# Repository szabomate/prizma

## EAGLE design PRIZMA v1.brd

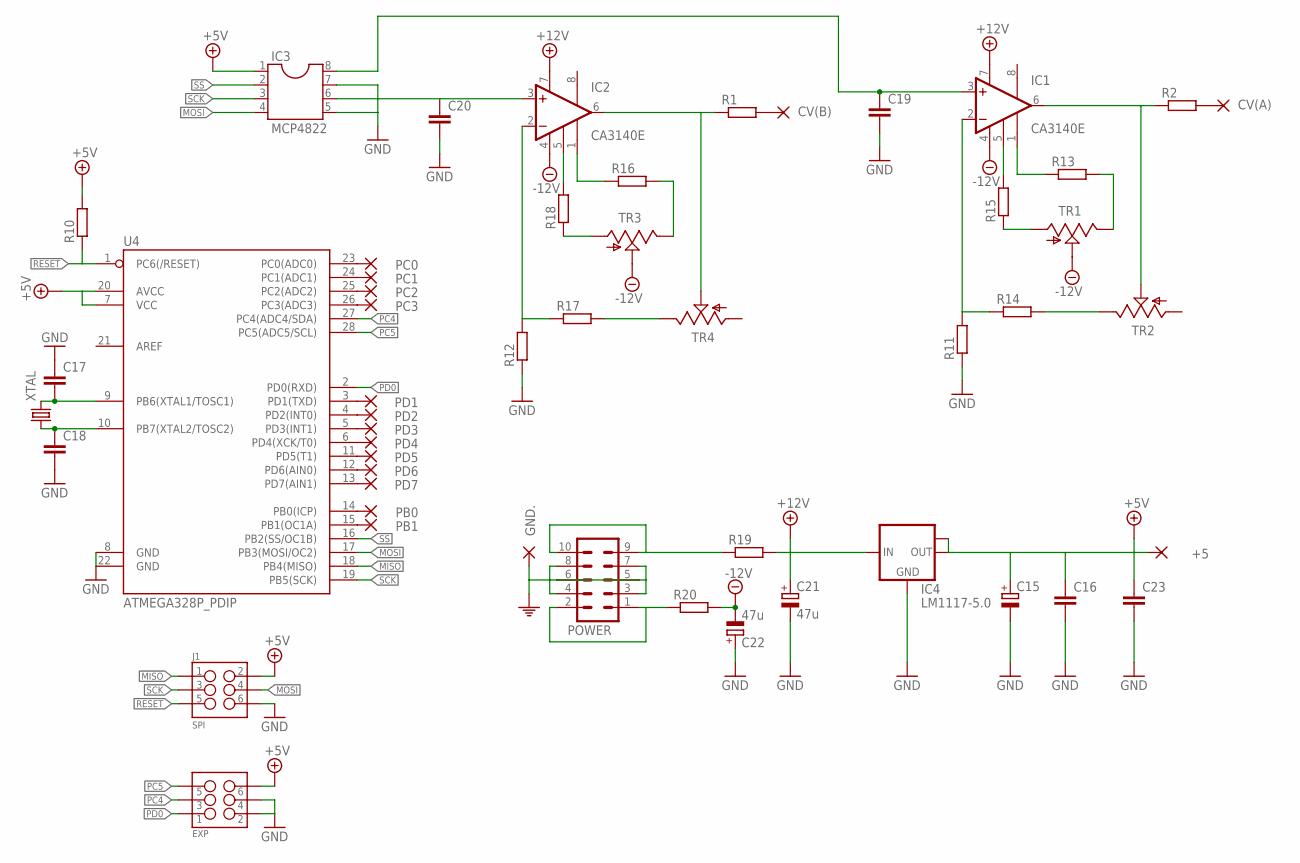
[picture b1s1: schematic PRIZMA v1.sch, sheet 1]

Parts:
+5: 2,0/0,9-O
C15: CPOL-EUC; PANASONIC_C
C16, C17, C18, C19, C20, C23: C-EUC0603; C0603
C21, C22: 47u; PANASONIC_D
CV(A): 2,0/0,9-O
CV(B): 2,0/0,9-R
EXP: M03X2NO_SILK; 2X3-NS
GND.: 2,0/0,9-O
IC1, IC2: CA3140E; DIL08
IC3: MCP4822; DIL08
IC4: LM1117-5.0; SOT223
J1: SPI; 2X3-NS
PB0, PB1: 2,0/0,9-O
PC0, PC1, PC2, PC3: 2,0/0,9-O
PD1, PD2, PD3, PD4, PD5, PD6, PD7: 2,0/0,9-O
POWER: M05X2SHD; 2X5-SHROUDED
R1, R2, R10, R11, R12, R13, R14, R15, R16, R17, R18, R19, R20: R-EU_R0603; R0603
TR1, TR2, TR3, TR4: TRIM_US-RJ9W; RJ9W
U4: ATMEGA328P_PDIP; DIL28-3
XTAL: CRYSTALSMD; HC49UP

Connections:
+5V: +5.1, C15.+, C16.1, C23.1, EXP.6, IC3.1, IC4.2 (OUT), IC4.TAB (OUT1), J1.2, R10.2, U4.7 (VCC), U4.20 (AVCC)
+12V: C21.+, IC1.7 (V+), IC2.7 (V+), IC4.3 (IN), R19.2
-12V: C22.-, IC1.4 (V-), IC2.4 (V-), R20.2, TR1.S, TR3.S
MISO: J1.1, U4.18 (PB4(MISO))
MOSI: IC3.4, J1.4, U4.17 (PB3(MOSI/OC2))
unnamed: IC1.5 (COMP), R15.2
unnamed: R15.1, TR1.A
unnamed: IC1.1 (BAL1), R13.1
unnamed: R13.2, TR1.E
unnamed: C19.1, IC1.3 (+IN), IC3.8
unnamed: IC1.2 (-IN), R11.2, R14.1
unnamed: IC1.6 (OUT), R2.1, TR2.S
unnamed: R14.2, TR2.E
unnamed: IC2.5 (COMP), R18.2
unnamed: R18.1, TR3.A
unnamed: IC2.1 (BAL1), R16.1
unnamed: R16.2, TR3.E
unnamed: C20.1, IC2.3 (+IN), IC3.6
unnamed: IC2.2 (-IN), R12.2, R17.1
unnamed: IC2.6 (OUT), R1.1, TR4.S
unnamed: R17.2, TR4.E
unnamed: PD5.1, U4.11 (PD5(T1))
unnamed: PB1.1, U4.15 (PB1(OC1A))
unnamed: C17.2, U4.9 (PB6(XTAL1/TOSC1)), XTAL.2
unnamed: C18.1, U4.10 (PB7(XTAL2/TOSC2)), XTAL.1
unnamed: PD4.1, U4.6 (PD4(XCK/T0))
unnamed: PD7.1, U4.13 (PD7(AIN1))
unnamed: PD6.1, U4.12 (PD6(AIN0))
unnamed: PB0.1, U4.14 (PB0(ICP))
unnamed: PD2.1, U4.4 (PD2(INT0))
unnamed: PD3.1, U4.5 (PD3(INT1))
unnamed: POWER.1, POWER.2, R20.1
unnamed: PC0.1, U4.23 (PC0(ADC0))
unnamed: PC1.1, U4.24 (PC1(ADC1))
unnamed: PC2.1, U4.25 (PC2(ADC2))
unnamed: PC3.1, U4.26 (PC3(ADC3))
unnamed: POWER.9, POWER.10, R19.1
unnamed: PD1.1, U4.3 (PD1(TXD))
unnamed: CV(A).1, R2.2
unnamed: CV(B).1, R1.2
PC4: EXP.3, U4.27 (PC4(ADC4/SDA))
PC5: EXP.5, U4.28 (PC5(ADC5/SCL))
PD0: EXP.1, U4.2 (PD0(RXD))
PE: C15.-, C16.2, C17.1, C18.2, C19.2, C20.2, C21.-, C22.+, C23.2, EXP.2, EXP.4, GND..1, IC3.5, IC3.7, IC4.1 (GND), J1.6, POWER.3, POWER.4, POWER.5, POWER.6, POWER.7, POWER.8, R11.1, R12.1, U4.8 (GND), U4.22 (GND)
RESET: J1.5, R10.1, U4.1 (PC6(/RESET))
SCK: IC3.3, J1.3, U4.19 (PB5(SCK))
SS: IC3.2, U4.16 (PB2(SS/OC1B))

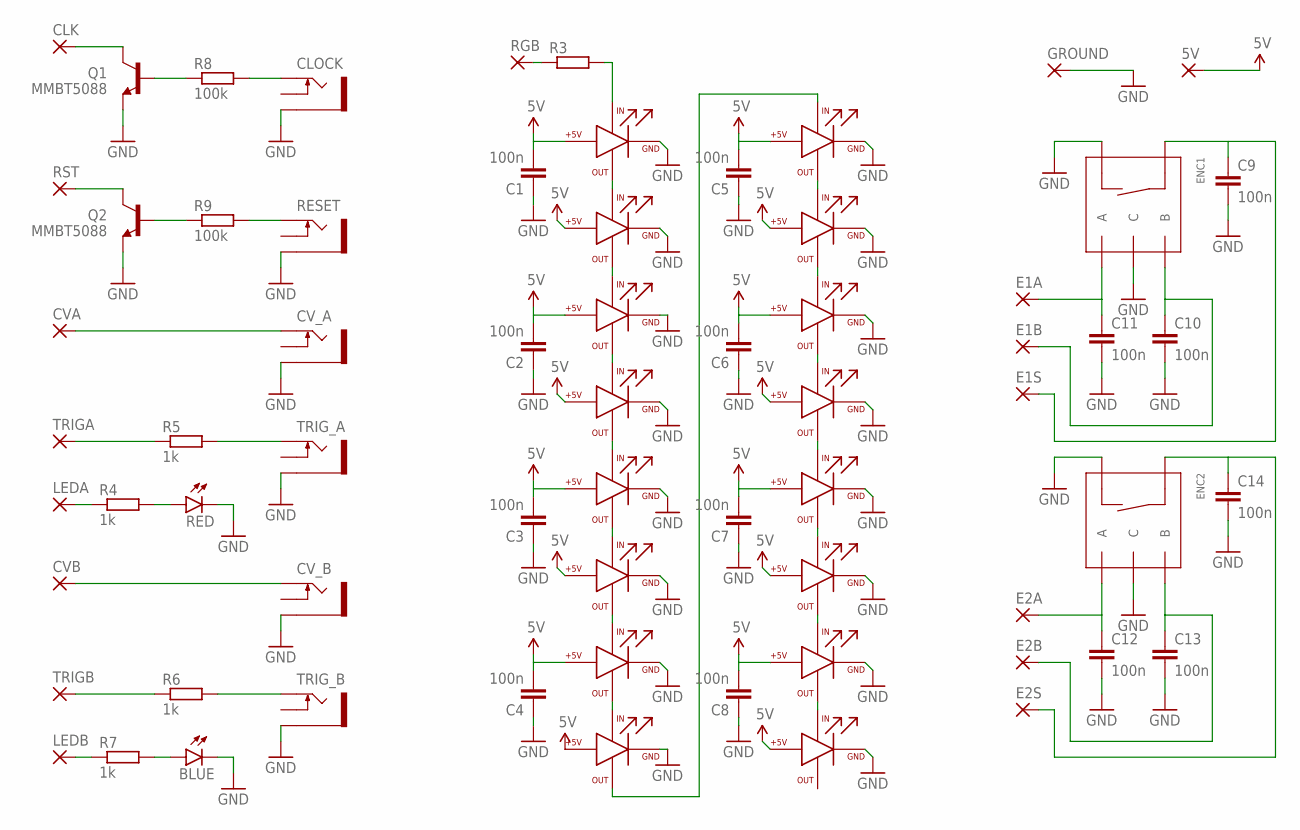
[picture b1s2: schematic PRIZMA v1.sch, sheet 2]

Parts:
5V: 2,0/0,9-R
BLUE: LED3MM
C1, C2, C3, C4, C5, C6, C7, C8, C9, C10, C11, C12, C13, C14: 100n; C0603
CLK: 2,0/0,9-O
CLOCK: THONKICONN
CVA: 2,0/0,9-R
CVB: 2,0/0,9-R
CV_A: THONKICONN
CV_B: THONKICONN
D1, D2, D3, D4, D5, D6, D7, D8, D13, D14, D15, D19, D20, D21, D22, D23: LED-RGB-CA-THRUCLEAR; LED-RGB-THRU
E1A, E1B, E1S, E2A, E2B, E2S: 2,0/0,9-O
ENC1, ENC2: ROTARTY_ENCODER; ROTARY_ENC_PLAIN
GROUND: 2,0/0,9-O
LEDA: 2,0/0,9-R
LEDB: 2,0/0,9-R
Q1, Q2: MMBT5088; SOT23-3
R3: R-EU_R0603; R0603
R4, R5, R6, R7: 1k; R0603
R8, R9: 100k; R0603
RED: LED3MM
RESET: THONKICONN
RGB: 2,0/0,9-O
RST: 2,0/0,9-O
TRIGA: 2,0/0,9-R
TRIGB: 2,0/0,9-R
TRIG_A: THONKICONN
TRIG_B: THONKICONN

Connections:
5V: 5V.1, C1.2, C2.2, C3.2, C4.2, C5.2, C6.2, C7.2, C8.2, D1.2 (+5V), D2.2 (+5V), D3.2 (+5V), D4.2 (+5V), D5.2 (+5V), D6.2 (+5V), D7.2 (+5V), D8.2 (+5V), D13.2 (+5V), D14.2 (+5V), D15.2 (+5V), D19.2 (+5V), D20.2 (+5V), D21.2 (+5V), D22.2 (+5V), D23.2 (+5V)
GND: BLUE.K (C), C1.1, C2.1, C3.1, C4.1, C5.1, C6.1, C7.1, C8.1, C9.2, C10.2, C11.2, C12.2, C13.2, C14.2, CLOCK.P$1 (5), CV_A.P$1 (5), CV_B.P$1 (5), D1.3 (GND), D2.3 (GND), D3.3 (GND), D4.3 (GND), D5.3 (GND), D6.3 (GND), D7.3 (GND), D8.3 (GND), D13.3 (GND), D14.3 (GND), D15.3 (GND), D19.3 (GND), D20.3 (GND), D21.3 (GND), D22.3 (GND), D23.3 (GND), ENC1.C, ENC1.SW-, ENC2.C, ENC2.SW-, GROUND.1, Q1.2 (E), Q2.2 (E), RED.K (C), RESET.P$1 (5), TRIG_A.P$1 (5), TRIG_B.P$1 (5)
unnamed: C11.1, E1A.1, ENC1.A
unnamed: C10.1, E1B.1, ENC1.B
unnamed: C12.1, E2A.1, ENC2.A
unnamed: C13.1, E2B.1, ENC2.B
unnamed: C14.1, E2S.1, ENC2.SW+
unnamed: C9.1, E1S.1, ENC1.SW+
unnamed: D19.1 (DATA_IN), R3.2
unnamed: Q1.1 (B), R8.1
unnamed: Q2.1 (B), R9.1
unnamed: CLK.1, Q1.3 (C)
unnamed: Q2.3 (C), RST.1
unnamed: CLOCK.P$3 (3), R8.2
unnamed: R9.2, RESET.P$3 (3)
unnamed: CVA.1, CV_A.P$3 (3)
unnamed: R5.1, TRIGA.1
unnamed: CVB.1, CV_B.P$3 (3)
unnamed: R5.2, TRIG_A.P$3 (3)
unnamed: D19.4 (DATA_OUT), D20.1 (DATA_IN)
unnamed: R4.2, RED.A
unnamed: BLUE.A, R7.2
unnamed: LEDB.1, R7.1
unnamed: LEDA.1, R4.1
unnamed: D20.4 (DATA_OUT), D21.1 (DATA_IN)
unnamed: R3.1, RGB.1
unnamed: D21.4 (DATA_OUT), D22.1 (DATA_IN)
unnamed: R6.1, TRIGB.1
unnamed: D22.4 (DATA_OUT), D23.1 (DATA_IN)
unnamed: R6.2, TRIG_B.P$3 (3)
unnamed: D13.1 (DATA_IN), D23.4 (DATA_OUT)
unnamed: D13.4 (DATA_OUT), D14.1 (DATA_IN)
unnamed: D14.4 (DATA_OUT), D15.1 (DATA_IN)
unnamed: D1.4 (DATA_OUT), D2.1 (DATA_IN)
unnamed: D2.4 (DATA_OUT), D3.1 (DATA_IN)
unnamed: D3.4 (DATA_OUT), D4.1 (DATA_IN)
unnamed: D4.4 (DATA_OUT), D5.1 (DATA_IN)
unnamed: D5.4 (DATA_OUT), D6.1 (DATA_IN)
unnamed: D6.4 (DATA_OUT), D7.1 (DATA_IN)
unnamed: D7.4 (DATA_OUT), D8.1 (DATA_IN)
unnamed: D1.1 (DATA_IN), D15.4 (DATA_OUT)

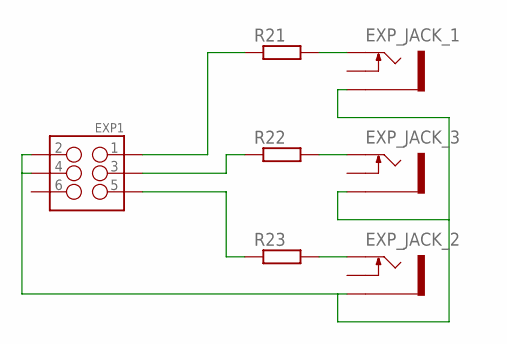
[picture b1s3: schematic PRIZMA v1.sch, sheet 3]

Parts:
EXP1: M03X2NO_SILK; 2X3-NS
EXP_JACK_1, EXP_JACK_2, EXP_JACK_3: THONKICONN
R21, R22, R23: R-EU_R0603; R0603

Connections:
unnamed: EXP1.2, EXP1.4, EXP_JACK_1.P$1 (5), EXP_JACK_2.P$1 (5), EXP_JACK_3.P$1 (5)
unnamed: EXP1.5, R23.1
unnamed: EXP1.3, R22.1
unnamed: EXP1.1, R21.1
unnamed: EXP_JACK_3.P$3 (3), R22.2
unnamed: EXP_JACK_2.P$3 (3), R23.2
unnamed: EXP_JACK_1.P$3 (3), R21.2

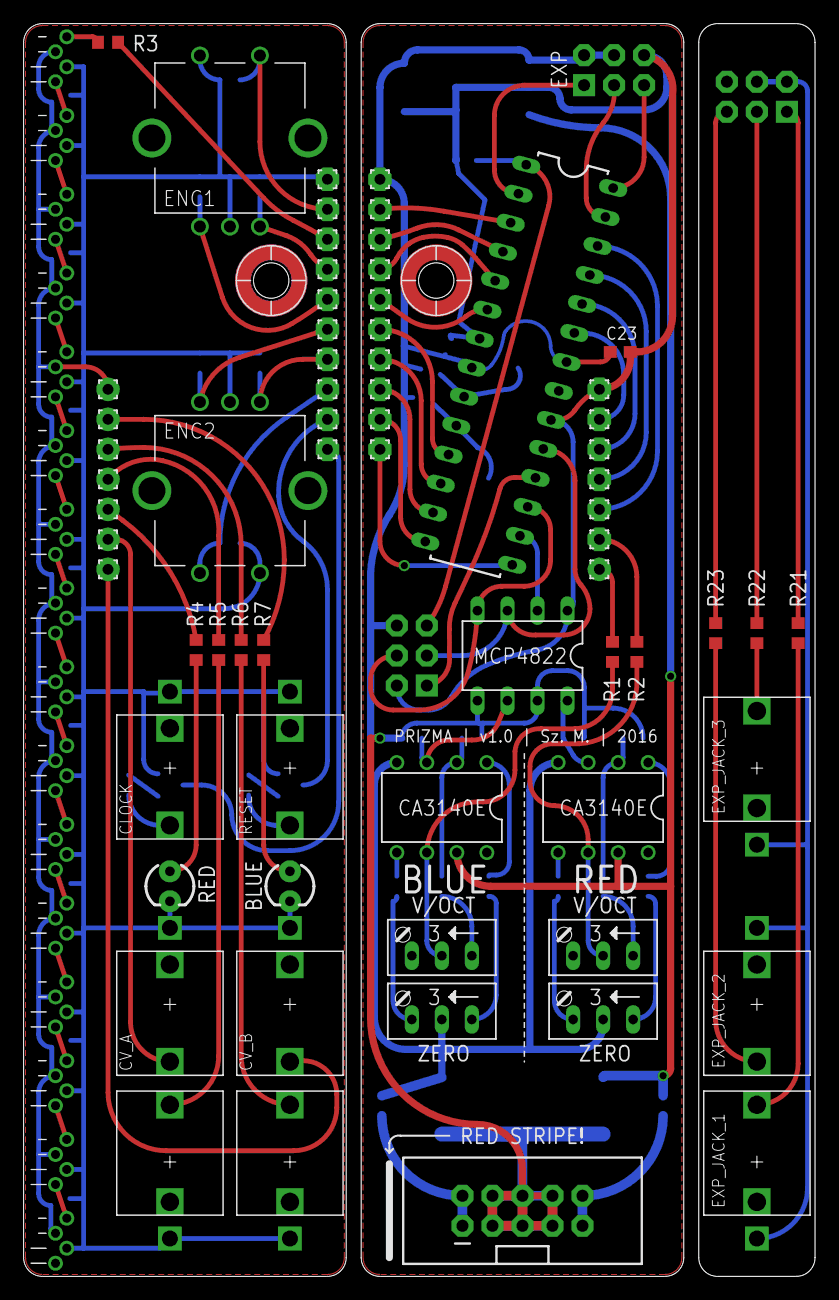
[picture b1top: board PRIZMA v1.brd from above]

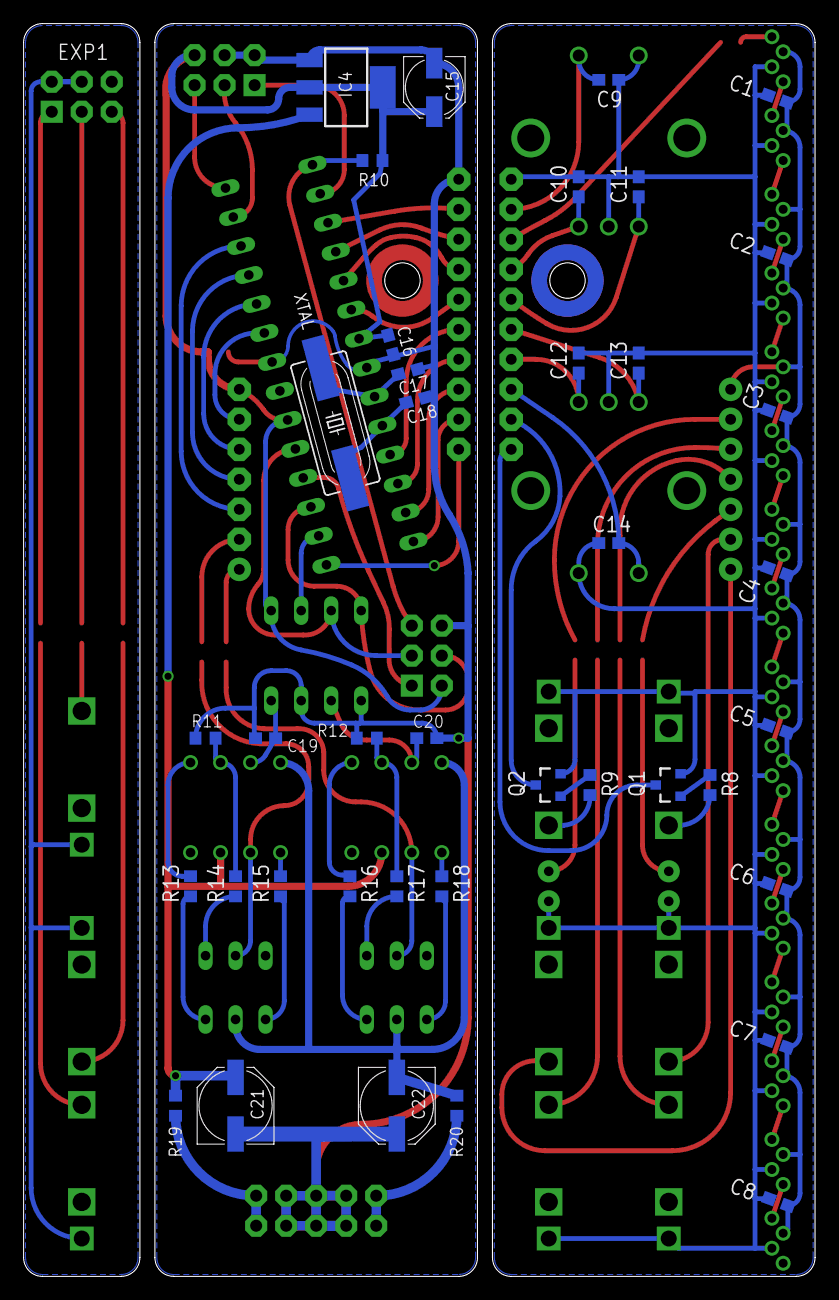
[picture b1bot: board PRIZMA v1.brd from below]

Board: 2 copper layers, 67.0 x 106.0 mm, 125 parts (40 on the bottom side), 95 nets.

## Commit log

2016-03-24 Added files via upload

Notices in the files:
parts and their libraries:
SparkFun-LED: Licensing: Creative Commons ShareAlike 4.0 International - https://creativecommons.org/licenses/by-sa/4.0
